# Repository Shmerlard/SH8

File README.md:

# The shmerlard 16

hi, my name is elad and Im an electrical engineering student in Ben gurion university.
I designed a small 16bit cpu, with a mix of jdh8, src, msp430 and the Hack computer.
this is still a work in progress, but so far it works.

I used logisim for the logic design, draw.io for the diagrams.
in order to see the working cpu in logisim: you need to build version `3.9.0` from source [here](https://github.com/logisim-evolution/logisim-evolution/blob/main/docs/developers.md), then just open the `.circ` file.

## Specs

- a common 16-bit data and address bus
- a total of 128kB of usable memory
- 6 GP register (up to 14 available)
- modular design for easy troubleshooting
- port for outside connections

## Contents

1) [Registers](/Wiki/Modules/Register-File.md)
2) [Instruction Register](/Wiki/Modules/Instruction-Register.md)
3) [Program Counter](/Wiki/Modules/Program-Counter.md)
4) [ALU](/Wiki/Modules/ALU.md)
5) [Control Unit](/Wiki/Modules/Control-Unit.md)
6) [Memory Registers](/Wiki/Modules/Memory-Registers.md)
7) [Condition Logic](/Wiki/Modules/Condition-Logic.md)
8) [Shift Control](/Wiki/Modules/Shift-Control.md)
9) [Gallery](/Wiki/Gallery.md)

## Instruction set

```text
0x00:  NOP
0x01:  MOV  Ra/#, Rb       | Ra/# -> Rb
0x02:  ST   Ra/#, Rb/#     | Ra/# -> M[Rb]/
0x03:  PUSH Ra/#           | Ra/# -> @SP; SP--
0x04:  POP  Ra             | SP++; @SP -> Ra
0x05:  ADD  Ra/#, Rb       | Ra/# + Rb -> Rb
0x06:  ADDC Ra/#, Rb       | Ra/# + Rb + c -> Rb
0x07:  SUB  Ra/#, Rb       | Rb - Ra/# -> Rb
0x08:  CMP  Ra/#, Rb       | Rb - Ra/#
0x09:  SHR  Ra/#, Rb       | SHR Rb (Ra/# times) -> Rb
0x0A:  SHL
0x0B:  RRC  Ra/#, Rb       | RRC Rb (Ra/# times) -> Rb
0x0C:  RLC
0x0D:  AND  Ra/#, Rb       | Ra/# AND Rb -> Rb
0x0E:  OR   Ra/#, Rb       | Ra/# OR  Rb -> Rb
0x0F:  XOR  Ra/#, Rb       | Ra/# XOR Rb -> Rb
0x10:  NOT
0x11:  CALL DST            | PC -> @SP; DST -> PC; SP-- -> SP;
0x12:  RET
0x13:  JMP  DST            | DST -> PC
```

for more simulated instructions see: [Simulated Instructions](/Wiki/Simulated-Instructions.md)

## [Registers](/Wiki/Modules/Register-File.md)

```text
0: SP/REG0  : STACK pointer    
1: SR/REG1  : Status register
2: REG2     : GP Input
3: REG3     : GP Output
4: REG3     : GP
5: REG4     : GP
6: REG5     : GP
7: REG6     : GP
```

## [Memory](/Wiki/Modules/Memory-Registers.md)

the memory ranges from `0x0000` to `0xFFFF`.
the memory is mapped in the following way:

```text
0x0000 - 0x7FFF: GP ROM              (32KiB    ROM)
0x8000 - 0xBFFF: GP RAM              (16KiB    RAM) 
0xC000 - 0xCFFF: VRAM                (4KiB    RAM) #CURRENTLY NOT IN USE#
0xD000 - 0xFFFF: NOT IN USE          (12KiB UNUSED)
```

## [Instruction format](./Wiki/Modules/Instruction-Register.md)

The instruction register is a 16-bit register

```text
the format is XXXX-XUMM-SSSS-DDDD
X = the opcode of the instruction
U = Currently not in use
M = indicates the addressing mode
S = indicates the source register
D = indicates the destination register
```

(see [addressing modes](/Wiki/Modules/Instruction-Register.md#addressing-modes)) for more info

## Full diagram

for the full gallery go to [Gallery](Wiki/Gallery.md)

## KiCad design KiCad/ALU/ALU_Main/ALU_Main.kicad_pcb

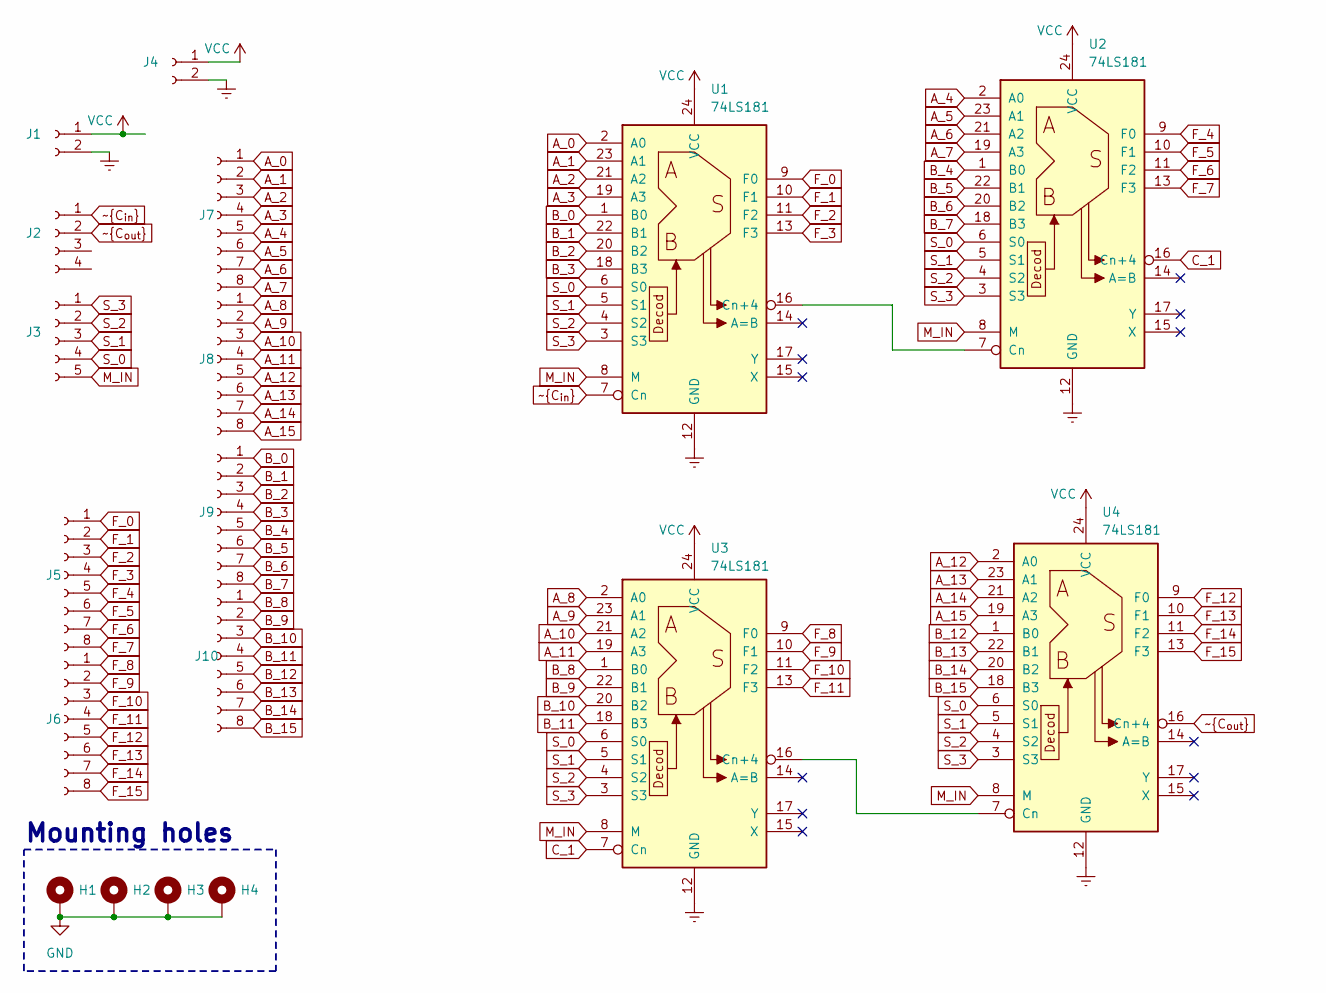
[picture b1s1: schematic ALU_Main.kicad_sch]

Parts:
H1, H2, H3, H4: MountingHole_Pad; MountingHole_2.2mm_M2_DIN965_Pad
J1, J4: Conn_01x02_Socket; JST_XH_S2B-XH-A-1_1x02_P2.50mm_Horizontal
J2: Conn_01x04_Socket; JST_XH_S4B-XH-A-1_1x04_P2.50mm_Horizontal
J3: Conn_01x05_Socket; JST_XH_S5B-XH-A-1_1x05_P2.50mm_Horizontal
J5, J6, J7, J8, J9, J10: Conn_01x08_Socket; JST_XH_S8B-XH-A-1_1x08_P2.50mm_Horizontal
U1, U2, U3, U4: 74LS181; DIP-24_W15.24mm_Socket_LongPads

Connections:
A_0: J7.1, U1.2 (A0)
A_1: J7.2, U1.23 (A1)
A_2: J7.3, U1.21 (A2)
A_3: J7.4, U1.19 (A3)
A_4: J7.5, U2.2 (A0)
A_5: J7.6, U2.23 (A1)
A_6: J7.7, U2.21 (A2)
A_7: J7.8, U2.19 (A3)
A_8: J8.1, U3.2 (A0)
A_9: J8.2, U3.23 (A1)
A_10: J8.3, U3.21 (A2)
A_11: J8.4, U3.19 (A3)
A_12: J8.5, U4.2 (A0)
A_13: J8.6, U4.23 (A1)
A_14: J8.7, U4.21 (A2)
A_15: J8.8, U4.19 (A3)
B_0: J9.1, U1.1 (B0)
B_1: J9.2, U1.22 (B1)
B_2: J9.3, U1.20 (B2)
B_3: J9.4, U1.18 (B3)
B_4: J9.5, U2.1 (B0)
B_5: J9.6, U2.22 (B1)
B_6: J9.7, U2.20 (B2)
B_7: J9.8, U2.18 (B3)
B_8: J10.1, U3.1 (B0)
B_9: J10.2, U3.22 (B1)
B_10: J10.3, U3.20 (B2)
B_11: J10.4, U3.18 (B3)
B_12: J10.5, U4.1 (B0)
B_13: J10.6, U4.22 (B1)
B_14: J10.7, U4.20 (B2)
B_15: J10.8, U4.18 (B3)
C_1: U2.16 (Cn+4), U3.7 (Cn)
F_0: J5.1, U1.9 (F0)
F_1: J5.2, U1.10 (F1)
F_2: J5.3, U1.11 (F2)
F_3: J5.4, U1.13 (F3)
F_4: J5.5, U2.9 (F0)
F_5: J5.6, U2.10 (F1)
F_6: J5.7, U2.11 (F2)
F_7: J5.8, U2.13 (F3)
F_8: J6.1, U3.9 (F0)
F_9: J6.2, U3.10 (F1)
F_10: J6.3, U3.11 (F2)
F_11: J6.4, U3.13 (F3)
F_12: J6.5, U4.9 (F0)
F_13: J6.6, U4.10 (F1)
F_14: J6.7, U4.11 (F2)
F_15: J6.8, U4.13 (F3)
GND: H1.1, H2.1, H3.1, H4.1, J1.2, J4.2, U1.12 (GND), U2.12 (GND), U3.12 (GND), U4.12 (GND)
M_IN: J3.5, U1.8 (M), U2.8 (M), U3.8 (M), U4.8 (M)
unnamed: U1.16 (Cn+4), U2.7 (Cn)
unnamed: U3.16 (Cn+4), U4.7 (Cn)
S_0: J3.4, U1.6 (S0), U2.6 (S0), U3.6 (S0), U4.6 (S0)
S_1: J3.3, U1.5 (S1), U2.5 (S1), U3.5 (S1), U4.5 (S1)
S_2: J3.2, U1.4 (S2), U2.4 (S2), U3.4 (S2), U4.4 (S2)
S_3: J3.1, U1.3 (S3), U2.3 (S3), U3.3 (S3), U4.3 (S3)
VCC: J1.1, J4.1, U1.24 (VCC), U2.24 (VCC), U3.24 (VCC), U4.24 (VCC)
~C_{in}: J2.1, U1.7 (Cn)
~C_{out}: J2.2, U4.16 (Cn+4)

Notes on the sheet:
Mounting holes

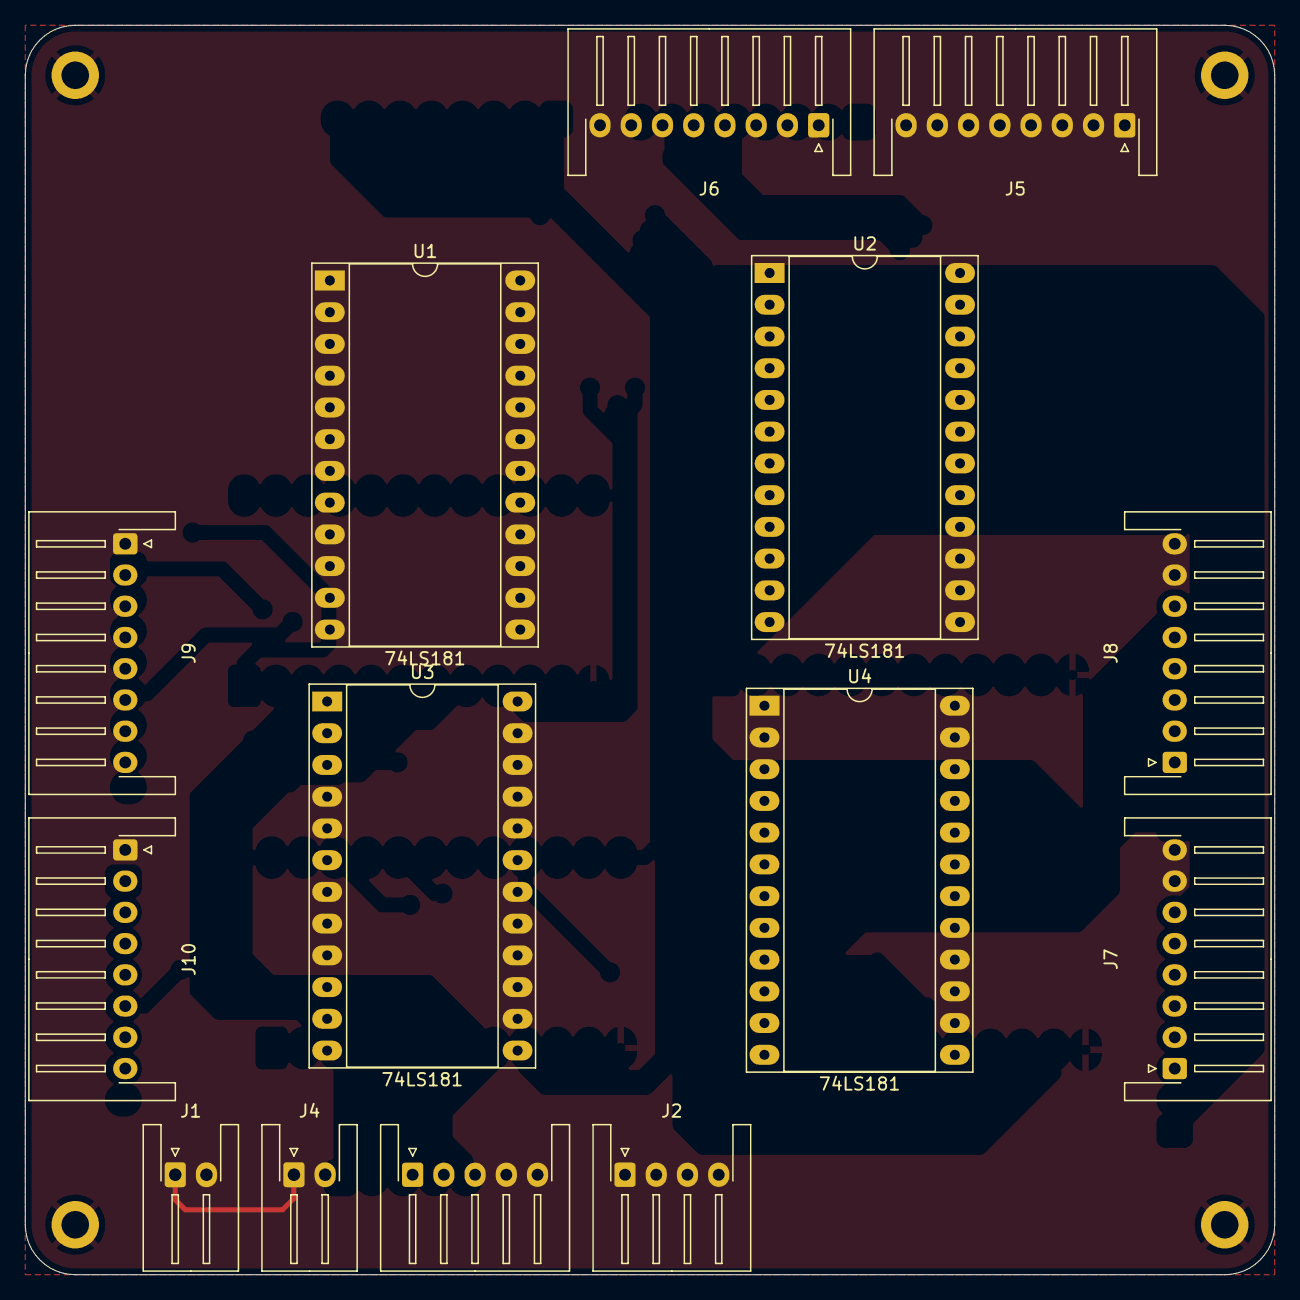
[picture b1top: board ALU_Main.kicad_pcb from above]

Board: 2 copper layers, 100.0 x 100.0 mm, 18 parts (0 on the bottom side), 60 nets.

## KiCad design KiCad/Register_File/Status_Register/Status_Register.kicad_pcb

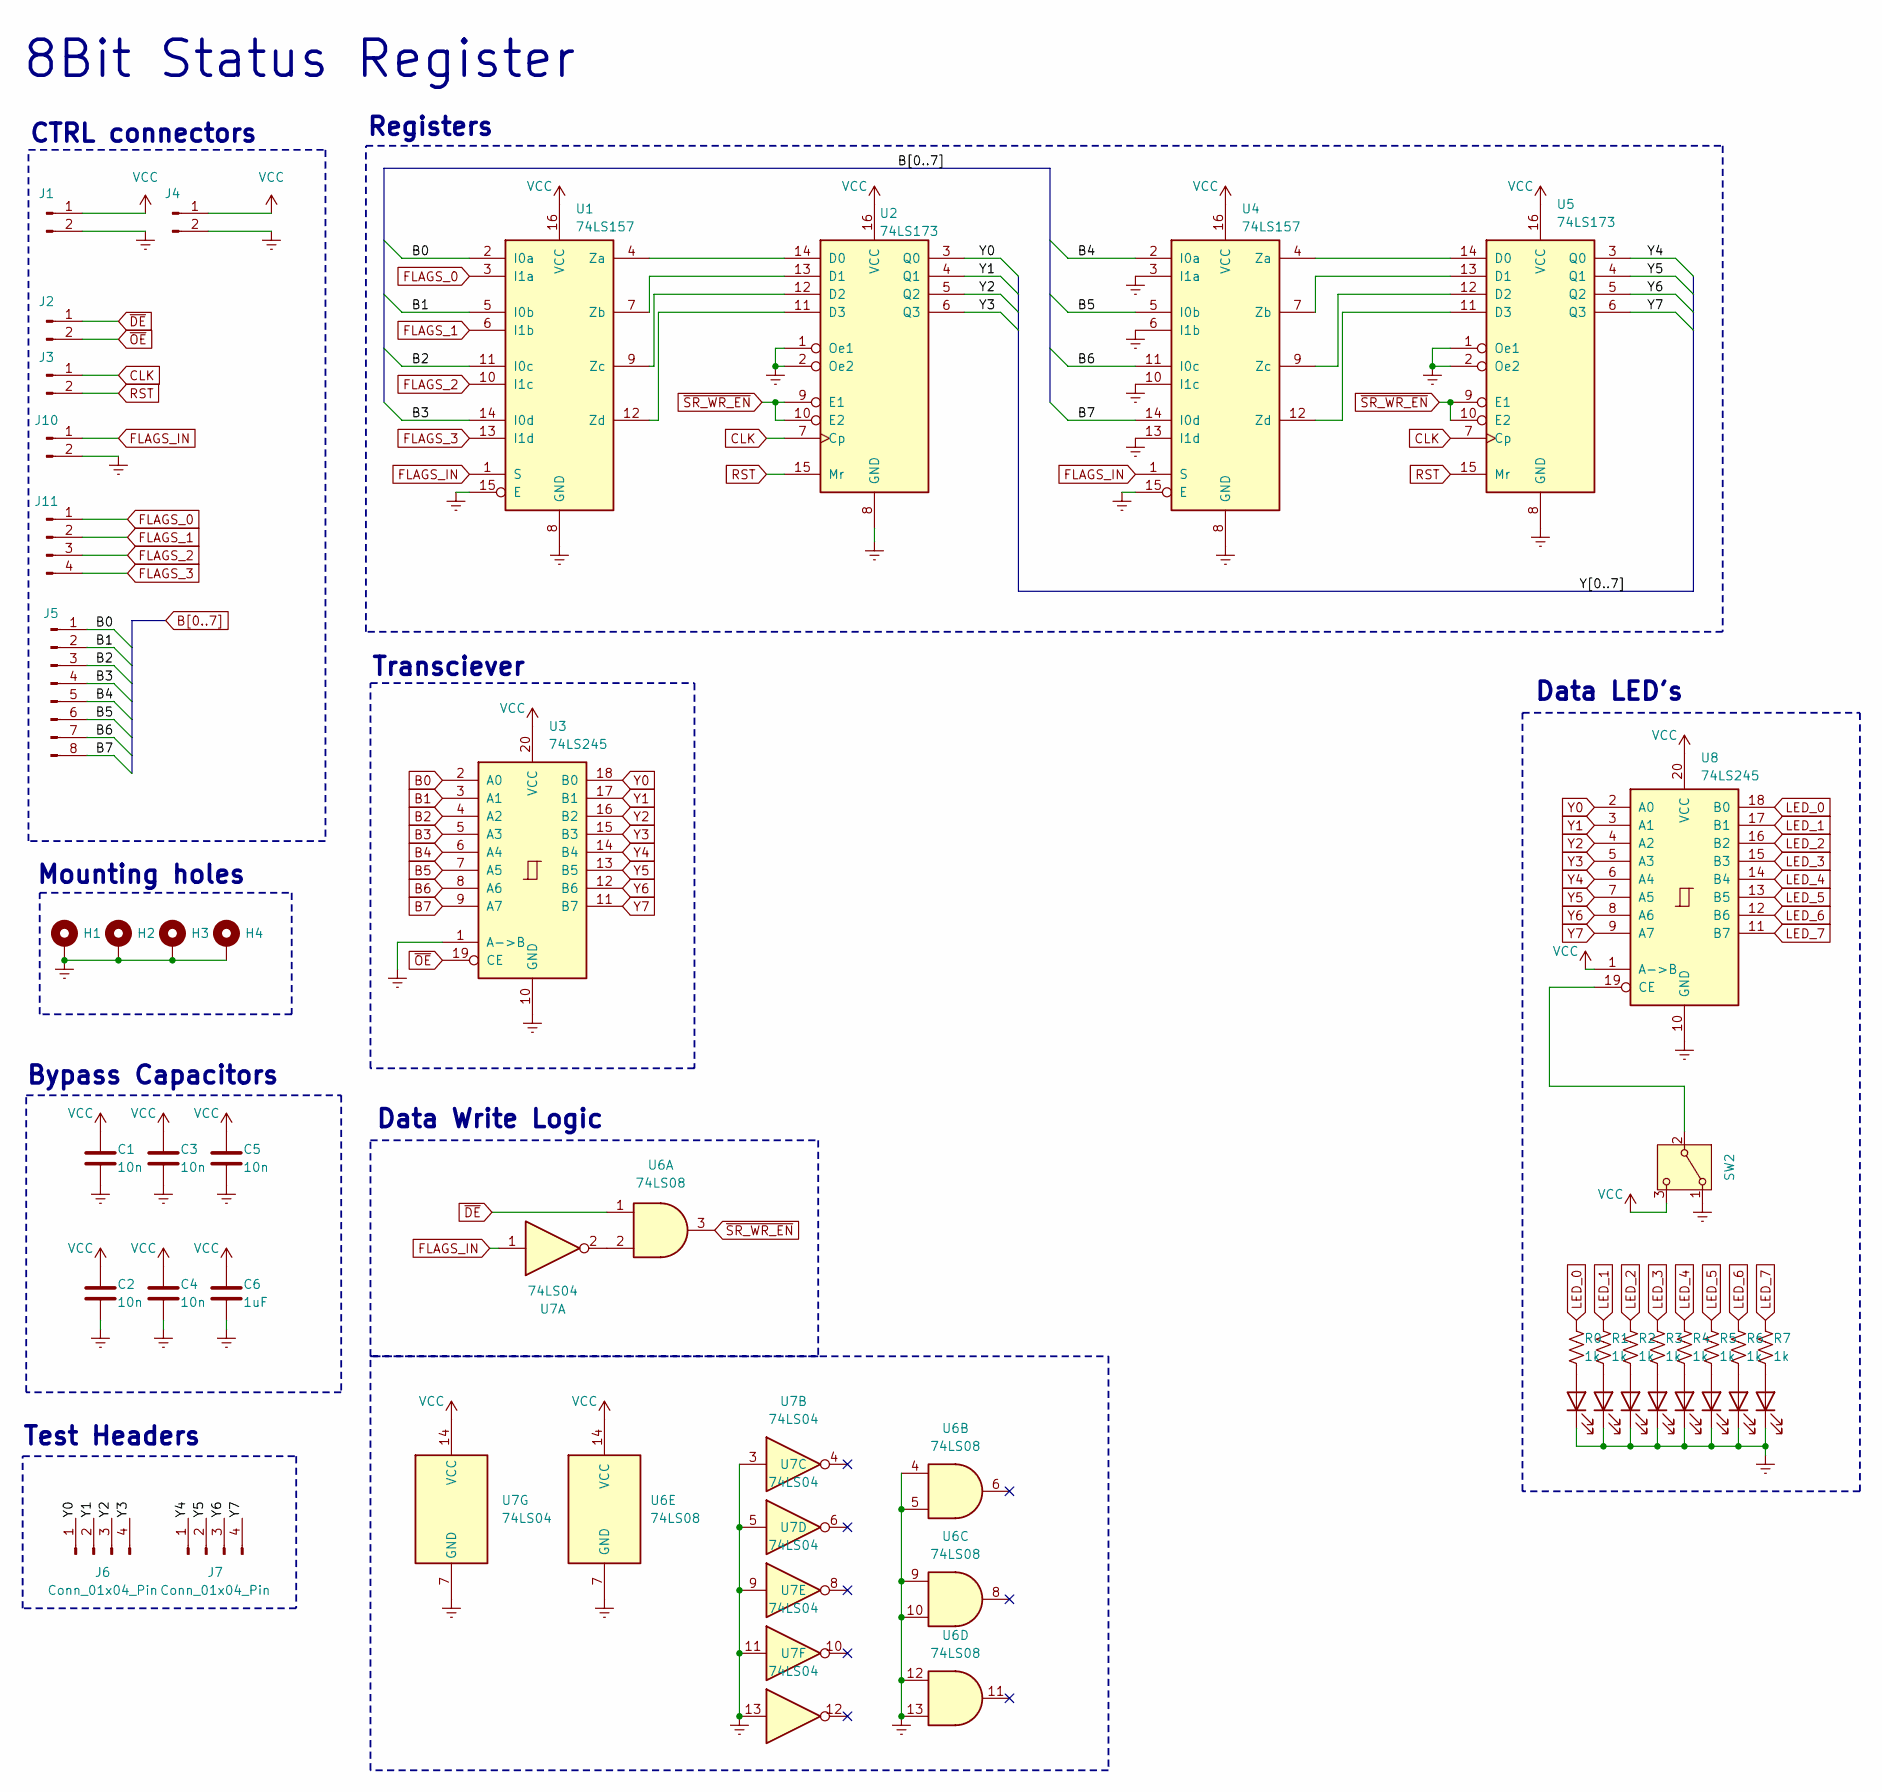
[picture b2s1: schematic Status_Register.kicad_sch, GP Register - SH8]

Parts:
C1, C2, C3, C4, C5: 10n; C_1206_3216Metric_Pad1.33x1.80mm_HandSolder
C6: 1uF; C_Radial_D6.3mm_H11.0mm_P2.50mm
D0, D1, D2, D3, D4, D5, D6, D7: LED; LED_Rectangular_W3.0mm_H2.0mm
H1, H2, H3, H4: MountingHole_Pad; MountingHole_2.2mm_M2_DIN965_Pad
J1, J2, J3, J4, J10: Conn_01x02_Pin; JST_XH_S2B-XH-A-1_1x02_P2.50mm_Horizontal
J5: Conn_01x08_Pin; JST_XH_S8B-XH-A-1_1x08_P2.50mm_Horizontal
J6, J7: Conn_01x04_Pin; PinHeader_1x04_P2.54mm_Vertical
J11: Conn_01x04_Pin; JST_XH_S4B-XH-A-1_1x04_P2.50mm_Horizontal
R0, R1, R2, R3, R4, R5, R6, R7: 1k; R_1206_3216Metric_Pad1.30x1.75mm_HandSolder
SW2: SW_SPDT; SW_Slide_SPDT_Angled_CK_OS102011MA1Q
U1, U4: 74LS157; DIP-16_W7.62mm_Socket_LongPads
U2, U5: 74LS173; DIP-16_W7.62mm_Socket_LongPads
U3, U8: 74LS245; DIP-20_W7.62mm_Socket_LongPads
U6: 74LS08; DIP-14_W7.62mm_Socket_LongPads
U7: 74LS04; DIP-14_W7.62mm_Socket_LongPads

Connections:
B0: J5.1, U1.2 (I0a), U3.2 (A0)
B1: J5.2, U1.5 (I0b), U3.3 (A1)
B2: J5.3, U1.11 (I0c), U3.4 (A2)
B3: J5.4, U1.14 (I0d), U3.5 (A3)
B4: J5.5, U3.6 (A4), U4.2 (I0a)
B5: J5.6, U3.7 (A5), U4.5 (I0b)
B6: J5.7, U3.8 (A6), U4.11 (I0c)
B7: J5.8, U3.9 (A7), U4.14 (I0d)
CLK: J3.1, U2.7 (Cp), U5.7 (Cp)
FLAGS_0: J11.1, U1.3 (I1a)
FLAGS_1: J11.2, U1.6 (I1b)
FLAGS_2: J11.3, U1.10 (I1c)
FLAGS_3: J11.4, U1.13 (I1d)
FLAGS_IN: J10.1, U1.1 (S), U4.1 (S), U7.1
GND: C1.2, C2.2, C3.2, C4.2, C5.2, C6.2, D0.1 (K), D1.1 (K), D2.1 (K), D3.1 (K), D4.1 (K), D5.1 (K), D6.1 (K), D7.1 (K), H1.1, H2.1, H3.1, H4.1, J1.2, J4.2, J10.2, SW2.1 (A), U1.8 (GND), U1.15 (E), U2.1 (Oe1), U2.2 (Oe2), U2.8 (GND), U3.1 (A->B), U3.10 (GND), U4.3 (I1a), U4.6 (I1b), U4.8 (GND), U4.10 (I1c), U4.13 (I1d), U4.15 (E), U5.1 (Oe1), U5.2 (Oe2), U5.8 (GND), U6.4, U6.5, U6.7 (GND), U6.9, U6.10, U6.12, U6.13, U7.3, U7.5, U7.7 (GND), U7.9, U7.11, U7.13, U8.10 (GND)
LED_0: R0.1, U8.18 (B0)
LED_1: R1.1, U8.17 (B1)
LED_2: R2.1, U8.16 (B2)
LED_3: R3.1, U8.15 (B3)
LED_4: R4.1, U8.14 (B4)
LED_5: R5.1, U8.13 (B5)
LED_6: R6.1, U8.12 (B6)
LED_7: R7.1, U8.11 (B7)
unnamed: D0.2 (A), R0.2
unnamed: D1.2 (A), R1.2
unnamed: D2.2 (A), R2.2
unnamed: D3.2 (A), R3.2
unnamed: D4.2 (A), R4.2
unnamed: D5.2 (A), R5.2
unnamed: D6.2 (A), R6.2
unnamed: D7.2 (A), R7.2
unnamed: SW2.2 (B), U8.19 (CE)
unnamed: U1.4 (Za), U2.14 (D0)
unnamed: U1.7 (Zb), U2.13 (D1)
unnamed: U1.9 (Zc), U2.12 (D2)
unnamed: U1.12 (Zd), U2.11 (D3)
unnamed: U4.4 (Za), U5.14 (D0)
unnamed: U4.7 (Zb), U5.13 (D1)
unnamed: U4.9 (Zc), U5.12 (D2)
unnamed: U4.12 (Zd), U5.11 (D3)
unnamed: U6.2, U7.2
RST: J3.2, U2.15 (Mr), U5.15 (Mr)
VCC: C1.1, C2.1, C3.1, C4.1, C5.1, C6.1, J1.1, J4.1, SW2.3 (C), U1.16 (VCC), U2.16 (VCC), U3.20 (VCC), U4.16 (VCC), U5.16 (VCC), U6.14 (VCC), U7.14 (VCC), U8.1 (A->B), U8.20 (VCC)
Y0: J6.1, U2.3 (Q0), U3.18 (B0), U8.2 (A0)
Y1: J6.2, U2.4 (Q1), U3.17 (B1), U8.3 (A1)
Y2: J6.3, U2.5 (Q2), U3.16 (B2), U8.4 (A2)
Y3: J6.4, U2.6 (Q3), U3.15 (B3), U8.5 (A3)
Y4: J7.1, U3.14 (B4), U5.3 (Q0), U8.6 (A4)
Y5: J7.2, U3.13 (B5), U5.4 (Q1), U8.7 (A5)
Y6: J7.3, U3.12 (B6), U5.5 (Q2), U8.8 (A6)
Y7: J7.4, U3.11 (B7), U5.6 (Q3), U8.9 (A7)
~DE: J2.1, U6.1
~OE: J2.2, U3.19 (CE)
~SR_WR_EN: U2.9 (E1), U2.10 (E2), U5.9 (E1), U5.10 (E2), U6.3

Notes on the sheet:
8Bit Status Register
Bypass Capacitors
Registers
Mounting holes
Data LED's
Test Headers
Data Write Logic
CTRL connectors
Transciever

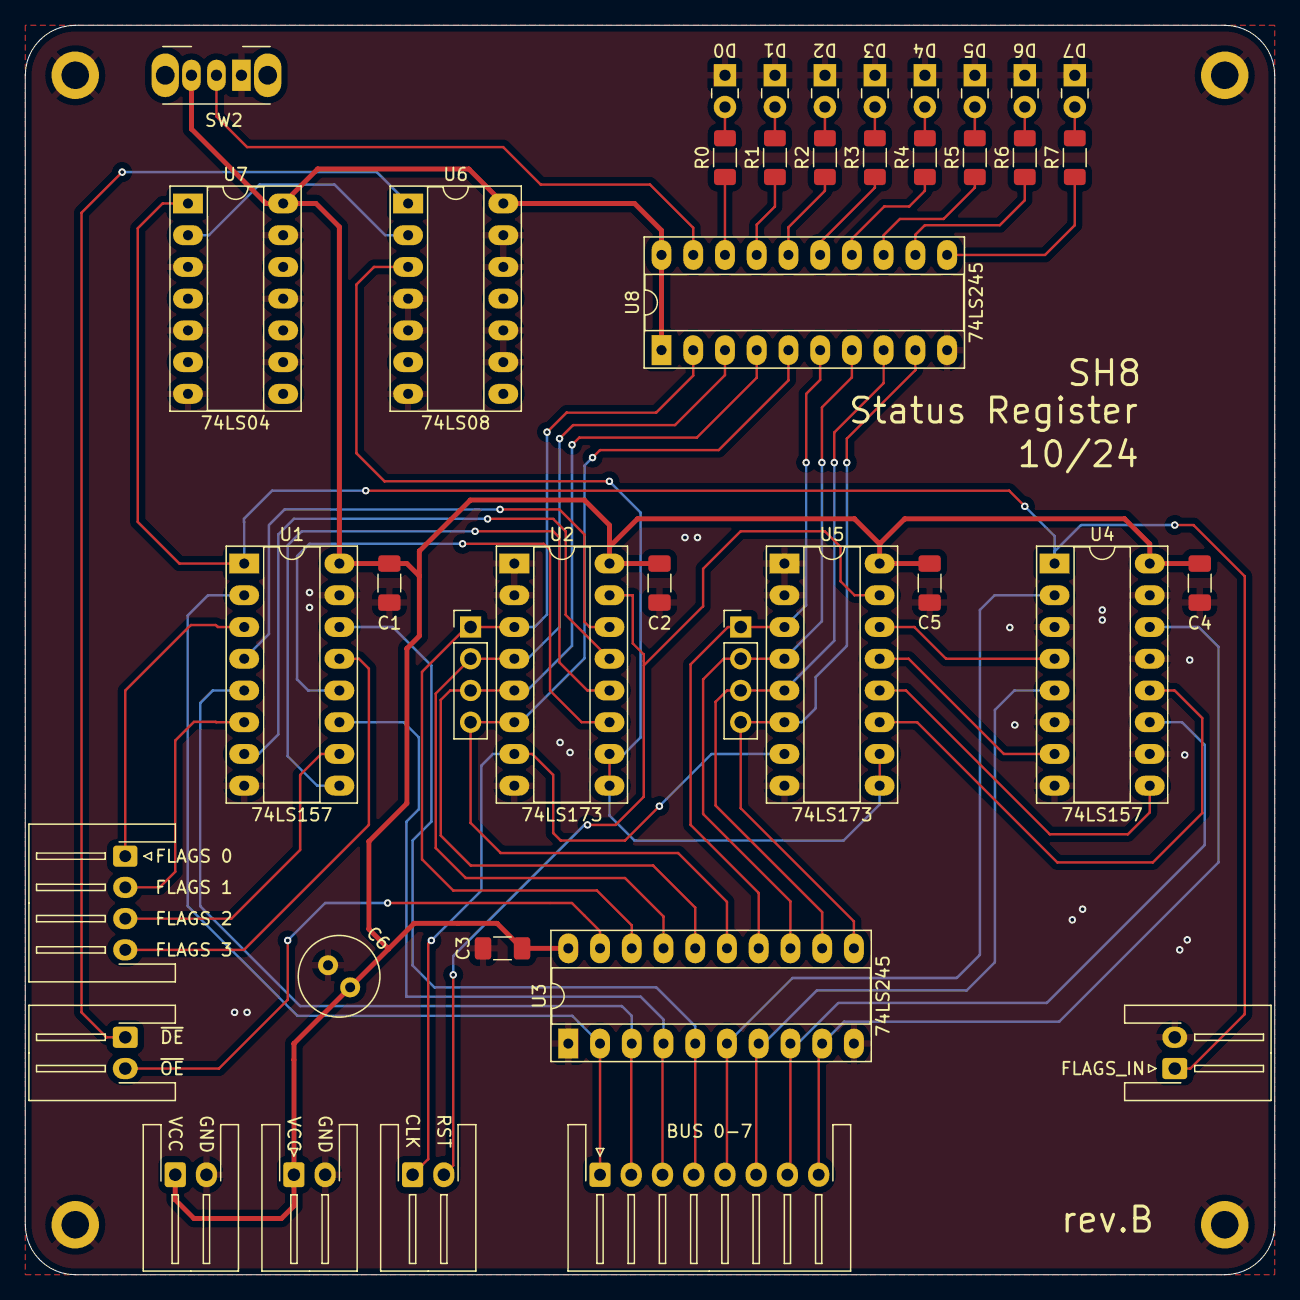
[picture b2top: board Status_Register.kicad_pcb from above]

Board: 2 copper layers, 100.0 x 100.0 mm, 44 parts (0 on the bottom side), 54 nets.

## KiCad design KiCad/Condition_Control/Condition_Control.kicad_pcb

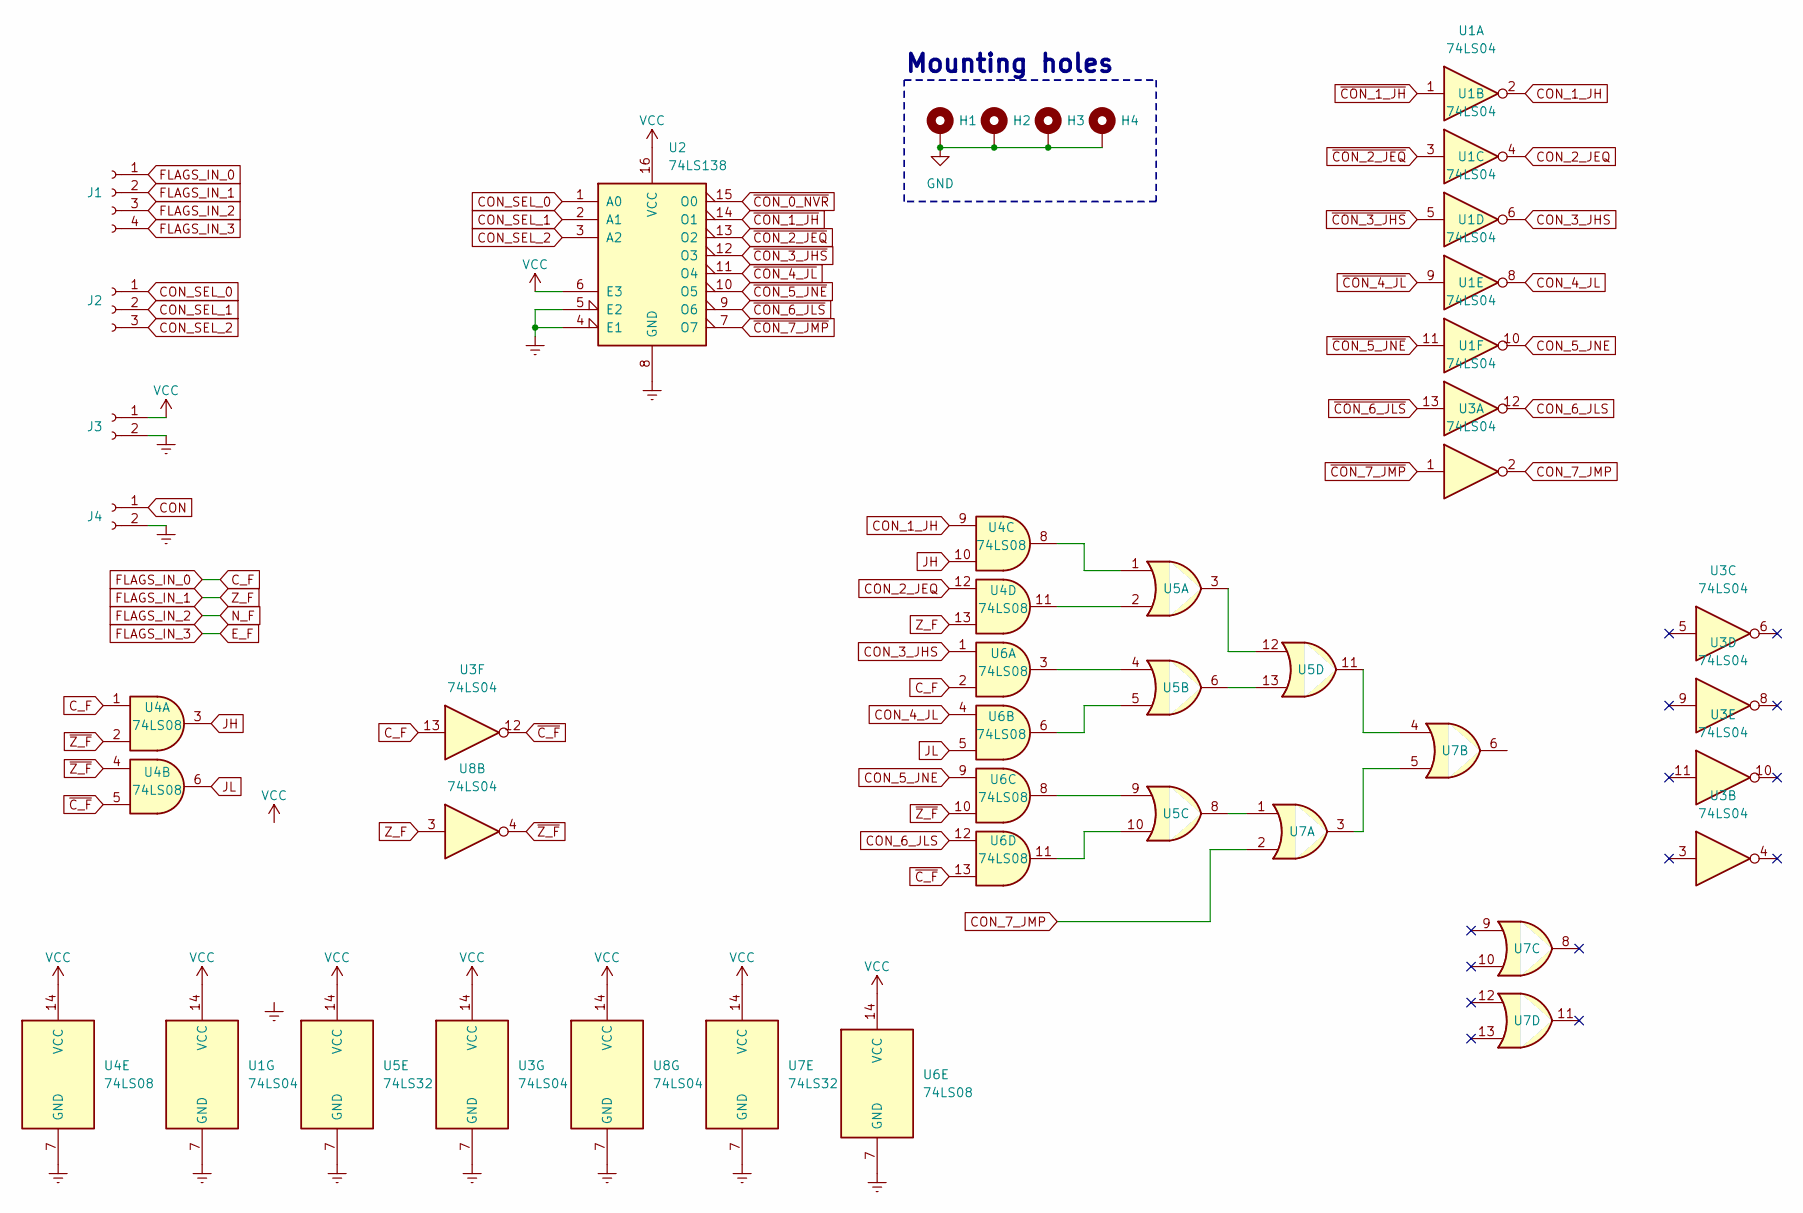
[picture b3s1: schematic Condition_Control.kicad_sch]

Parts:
H1, H2, H3, H4: MountingHole_Pad; MountingHole_2.2mm_M2_DIN965_Pad
J1: Conn_01x04_Socket; JST_XH_S4B-XH-A-1_1x04_P2.50mm_Horizontal
J2: Conn_01x03_Socket; JST_XH_S3B-XH-A-1_1x03_P2.50mm_Horizontal
J3, J4: Conn_01x02_Socket; JST_XH_S2B-XH-A-1_1x02_P2.50mm_Horizontal
U1, U3, U8: 74LS04; DIP-14_W7.62mm_Socket_LongPads
U2: 74LS138; DIP-16_W7.62mm_Socket_LongPads
U4, U6: 74LS08; DIP-14_W7.62mm_Socket_LongPads
U5, U7: 74LS32; DIP-14_W7.62mm_Socket_LongPads

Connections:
CON: J4.1
CON_1_JH: U1.2, U4.9
CON_2_JEQ: U1.4, U4.12
CON_3_JHS: U1.6, U6.1
CON_4_JL: U1.8, U6.4
CON_5_JNE: U1.10, U6.9
CON_6_JLS: U1.12, U6.12
CON_7_JMP: U3.2, U7.2
CON_SEL_0: J2.1, U2.1 (A0)
CON_SEL_1: J2.2, U2.2 (A1)
CON_SEL_2: J2.3, U2.3 (A2)
C_F: J1.1, U3.13, U4.1, U6.2
E_F: J1.4
FLAGS_IN_1: J1.2, U4.13, U8.3
FLAGS_IN_2: J1.3
GND: H1.1, H2.1, H3.1, H4.1, J3.2, J4.2, U1.7 (GND), U2.4 (E1), U2.5 (E2), U2.8 (GND), U3.7 (GND), U4.7 (GND), U5.7 (GND), U6.7 (GND), U7.7 (GND), U8.7 (GND)
JH: U4.3, U4.10
JL: U4.6, U6.5
unnamed: U4.8, U5.1
unnamed: U4.11, U5.2
unnamed: U5.4, U6.3
unnamed: U5.5, U6.6
unnamed: U5.8, U7.1
unnamed: U5.9, U6.8
unnamed: U5.10, U6.11
unnamed: U5.11, U7.4
unnamed: U5.3, U5.12
unnamed: U5.6, U5.13
unnamed: U7.3, U7.5
VCC: J3.1, U1.14 (VCC), U2.6 (E3), U2.16 (VCC), U3.14 (VCC), U4.14 (VCC), U5.14 (VCC), U6.14 (VCC), U7.14 (VCC), U8.14 (VCC)
~CON_0_NVR: U2.15 (O0)
~CON_1_JH: U1.1, U2.14 (O1)
~CON_2_JEQ: U1.3, U2.13 (O2)
~CON_3_JHS: U1.5, U2.12 (O3)
~CON_4_JL: U1.9, U2.11 (O4)
~CON_5_JNE: U1.11, U2.10 (O5)
~CON_6_JLS: U1.13, U2.9 (O6)
~CON_7_JMP: U2.7 (O7), U3.1
~C_F: U3.12, U4.5, U6.13
~Z_F: U4.2, U4.4, U6.10, U8.4

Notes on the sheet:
Mounting holes

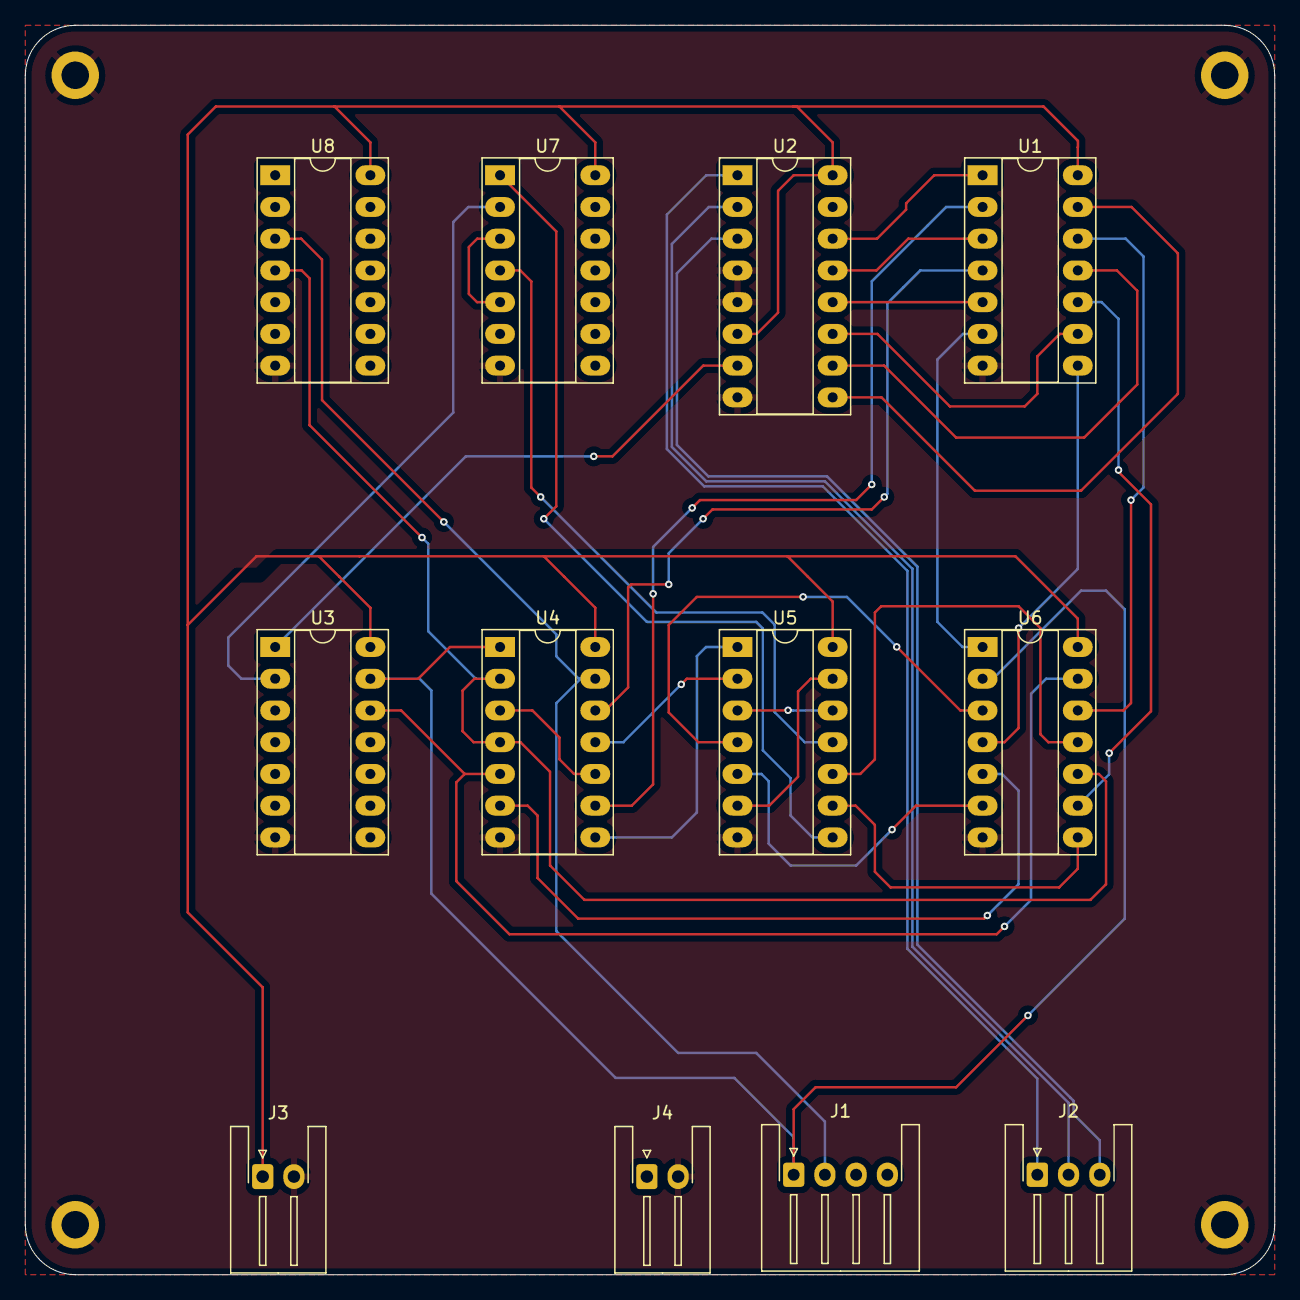
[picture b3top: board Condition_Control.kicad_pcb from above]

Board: 2 copper layers, 100.0 x 100.0 mm, 16 parts (0 on the bottom side), 36 nets.

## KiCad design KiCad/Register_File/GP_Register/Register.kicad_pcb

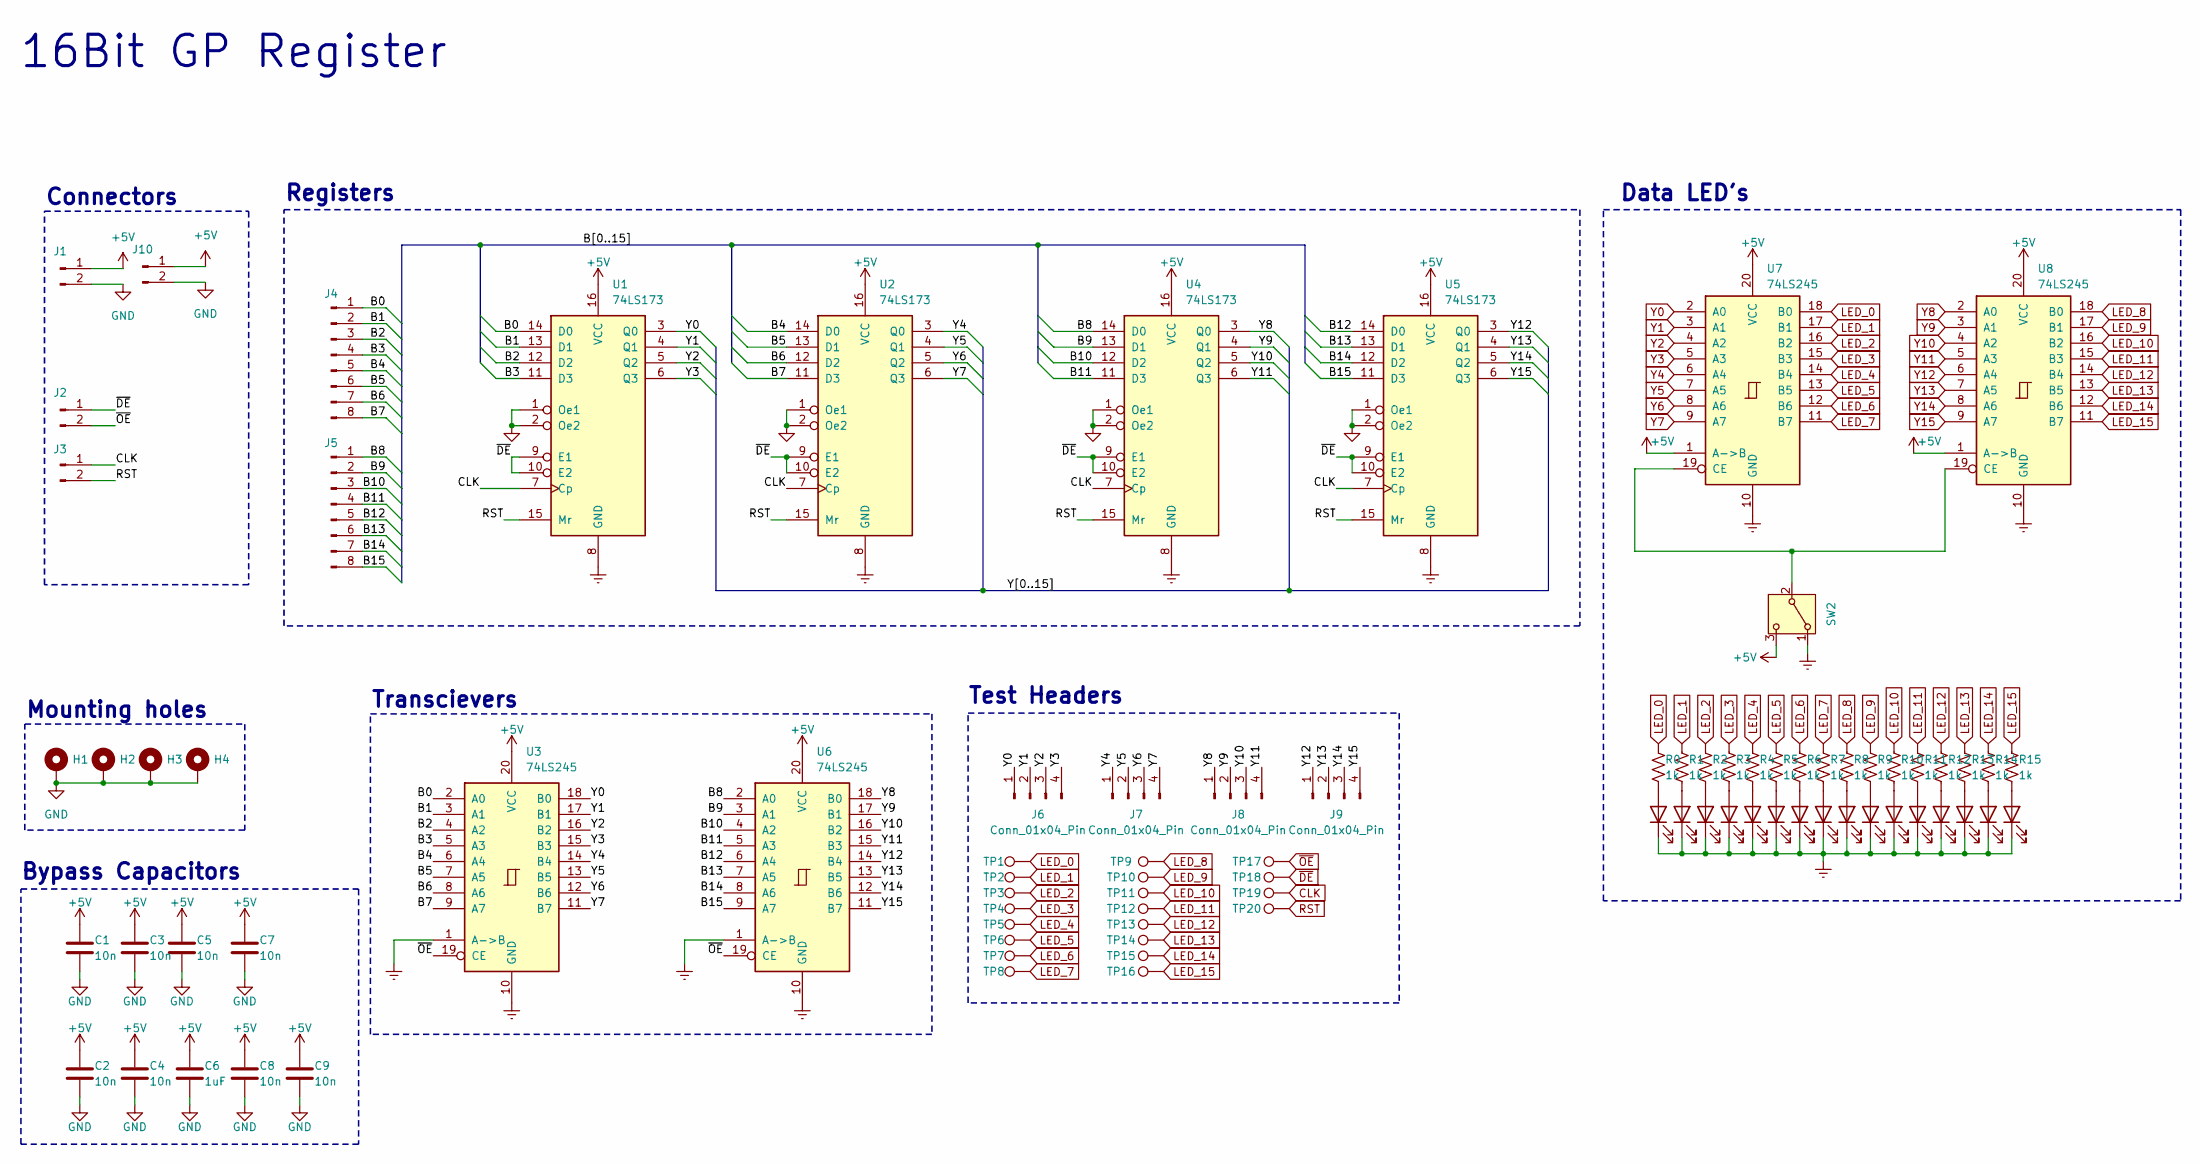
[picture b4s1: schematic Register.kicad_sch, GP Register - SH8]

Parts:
C1, C2, C3, C4, C5, C7, C8, C9: 10n; C_1206_3216Metric_Pad1.33x1.80mm_HandSolder
C6: 1uF; C_Radial_D6.3mm_H11.0mm_P2.50mm
D0, D1, D2, D3, D4, D5, D6, D7, D8, D9, D10, D11, D12, D13, D14, D15: LED; LED_Rectangular_W3.0mm_H2.0mm
H1, H2, H3, H4: MountingHole_Pad; MountingHole_2.2mm_M2_DIN965_Pad
J1, J2, J3, J10: Conn_01x02_Pin; JST_XH_S2B-XH-A-1_1x02_P2.50mm_Horizontal_fixed
J4, J5: Conn_01x08_Pin; JST_XH_S8B-XH-A-1_1x08_P2.50mm_Horizontal
J6, J7, J8, J9: Conn_01x04_Pin; PinHeader_1x04_P2.54mm_Vertical
R0, R1, R2, R3, R4, R5, R6, R7, R8, R9, R10, R11, R12, R13, R14, R15: 1k; R_1206_3216Metric_Pad1.30x1.75mm_HandSolder
SW2: SW_SPDT; SW_Slide_SPDT_Angled_CK_OS102011MA1Q
TP1, TP2, TP3, TP4, TP5, TP6, TP7, TP8, TP9, TP10, TP11, TP12, TP13, TP14, TP15, TP16, TP17, TP18, TP19, TP20: TestPoint; TestPoint_Pad_D1.0mm
U1, U2, U4, U5: 74LS173; DIP-16_W7.62mm_Socket_LongPads
U3, U6, U7, U8: 74LS245; DIP-20_W7.62mm_Socket_LongPads

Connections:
+5V: C1.1, C2.1, C3.1, C4.1, C5.1, C6.1, C7.1, C8.1, C9.1, J1.1, J10.1, SW2.3 (C), U1.16 (VCC), U2.16 (VCC), U3.20 (VCC), U4.16 (VCC), U5.16 (VCC), U6.20 (VCC), U7.1 (A->B), U7.20 (VCC), U8.1 (A->B), U8.20 (VCC)
/B0: J4.1, U1.14 (D0), U3.2 (A0)
/B1: J4.2, U1.13 (D1), U3.3 (A1)
/B2: J4.3, U1.12 (D2), U3.4 (A2)
/B3: J4.4, U1.11 (D3), U3.5 (A3)
/B4: J4.5, U2.14 (D0), U3.6 (A4)
/B5: J4.6, U2.13 (D1), U3.7 (A5)
/B6: J4.7, U2.12 (D2), U3.8 (A6)
/B7: J4.8, U2.11 (D3), U3.9 (A7)
/B8: J5.1, U4.14 (D0), U6.2 (A0)
/B9: J5.2, U4.13 (D1), U6.3 (A1)
/B10: J5.3, U4.12 (D2), U6.4 (A2)
/B11: J5.4, U4.11 (D3), U6.5 (A3)
/B12: J5.5, U5.14 (D0), U6.6 (A4)
/B13: J5.6, U5.13 (D1), U6.7 (A5)
/B14: J5.7, U5.12 (D2), U6.8 (A6)
/B15: J5.8, U5.11 (D3), U6.9 (A7)
CLK: J3.1, TP19.1, U1.7 (Cp), U2.7 (Cp), U4.7 (Cp), U5.7 (Cp)
GND: C1.2, C2.2, C3.2, C4.2, C5.2, C6.2, C7.2, C8.2, C9.2, D0.1 (K), D1.1 (K), D2.1 (K), D3.1 (K), D4.1 (K), D5.1 (K), D6.1 (K), D7.1 (K), D8.1 (K), D9.1 (K), D10.1 (K), D11.1 (K), D12.1 (K), D13.1 (K), D14.1 (K), D15.1 (K), H1.1, H2.1, H3.1, H4.1, J1.2, J10.2, SW2.1 (A), U1.1 (Oe1), U1.2 (Oe2), U1.8 (GND), U2.1 (Oe1), U2.2 (Oe2), U2.8 (GND), U3.1 (A->B), U3.10 (GND), U4.1 (Oe1), U4.2 (Oe2), U4.8 (GND), U5.1 (Oe1), U5.2 (Oe2), U5.8 (GND), U6.1 (A->B), U6.10 (GND), U7.10 (GND), U8.10 (GND)
LED_0: R0.1, TP1.1, U7.18 (B0)
LED_1: R1.1, TP2.1, U7.17 (B1)
LED_2: R2.1, TP3.1, U7.16 (B2)
LED_3: R3.1, TP4.1, U7.15 (B3)
LED_4: R4.1, TP5.1, U7.14 (B4)
LED_5: R5.1, TP6.1, U7.13 (B5)
LED_6: R6.1, TP7.1, U7.12 (B6)
LED_7: R7.1, TP8.1, U7.11 (B7)
LED_8: R8.1, TP9.1, U8.18 (B0)
LED_9: R9.1, TP10.1, U8.17 (B1)
LED_10: R10.1, TP11.1, U8.16 (B2)
LED_11: R11.1, TP12.1, U8.15 (B3)
LED_12: R12.1, TP13.1, U8.14 (B4)
LED_13: R13.1, TP14.1, U8.13 (B5)
LED_14: R14.1, TP15.1, U8.12 (B6)
LED_15: R15.1, TP16.1, U8.11 (B7)
unnamed: D0.2 (A), R0.2
unnamed: D1.2 (A), R1.2
unnamed: D2.2 (A), R2.2
unnamed: D3.2 (A), R3.2
unnamed: D4.2 (A), R4.2
unnamed: D5.2 (A), R5.2
unnamed: D6.2 (A), R6.2
unnamed: D7.2 (A), R7.2
unnamed: D8.2 (A), R8.2
unnamed: D9.2 (A), R9.2
unnamed: D10.2 (A), R10.2
unnamed: D11.2 (A), R11.2
unnamed: D12.2 (A), R12.2
unnamed: D13.2 (A), R13.2
unnamed: D14.2 (A), R14.2
unnamed: D15.2 (A), R15.2
unnamed: SW2.2 (B), U7.19 (CE), U8.19 (CE)
RST: J3.2, TP20.1, U1.15 (Mr), U2.15 (Mr), U4.15 (Mr), U5.15 (Mr)
Y0: J6.1, U1.3 (Q0), U3.18 (B0), U7.2 (A0)
Y1: J6.2, U1.4 (Q1), U3.17 (B1), U7.3 (A1)
Y2: J6.3, U1.5 (Q2), U3.16 (B2), U7.4 (A2)
Y3: J6.4, U1.6 (Q3), U3.15 (B3), U7.5 (A3)
Y4: J7.1, U2.3 (Q0), U3.14 (B4), U7.6 (A4)
Y5: J7.2, U2.4 (Q1), U3.13 (B5), U7.7 (A5)
Y6: J7.3, U2.5 (Q2), U3.12 (B6), U7.8 (A6)
Y7: J7.4, U2.6 (Q3), U3.11 (B7), U7.9 (A7)
Y8: J8.1, U4.3 (Q0), U6.18 (B0), U8.2 (A0)
Y9: J8.2, U4.4 (Q1), U6.17 (B1), U8.3 (A1)
Y10: J8.3, U4.5 (Q2), U6.16 (B2), U8.4 (A2)
Y11: J8.4, U4.6 (Q3), U6.15 (B3), U8.5 (A3)
Y12: J9.1, U5.3 (Q0), U6.14 (B4), U8.6 (A4)
Y13: J9.2, U5.4 (Q1), U6.13 (B5), U8.7 (A5)
Y14: J9.3, U5.5 (Q2), U6.12 (B6), U8.8 (A6)
Y15: J9.4, U5.6 (Q3), U6.11 (B7), U8.9 (A7)
~DE: J2.1, TP18.1, U1.9 (E1), U1.10 (E2), U2.9 (E1), U2.10 (E2), U4.9 (E1), U4.10 (E2), U5.9 (E1), U5.10 (E2)
~OE: J2.2, TP17.1, U3.19 (CE), U6.19 (CE)

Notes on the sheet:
16Bit GP Register
Data LED's
Bypass Capacitors
Registers
Mounting holes
Test Headers
Connectors
Transcievers
